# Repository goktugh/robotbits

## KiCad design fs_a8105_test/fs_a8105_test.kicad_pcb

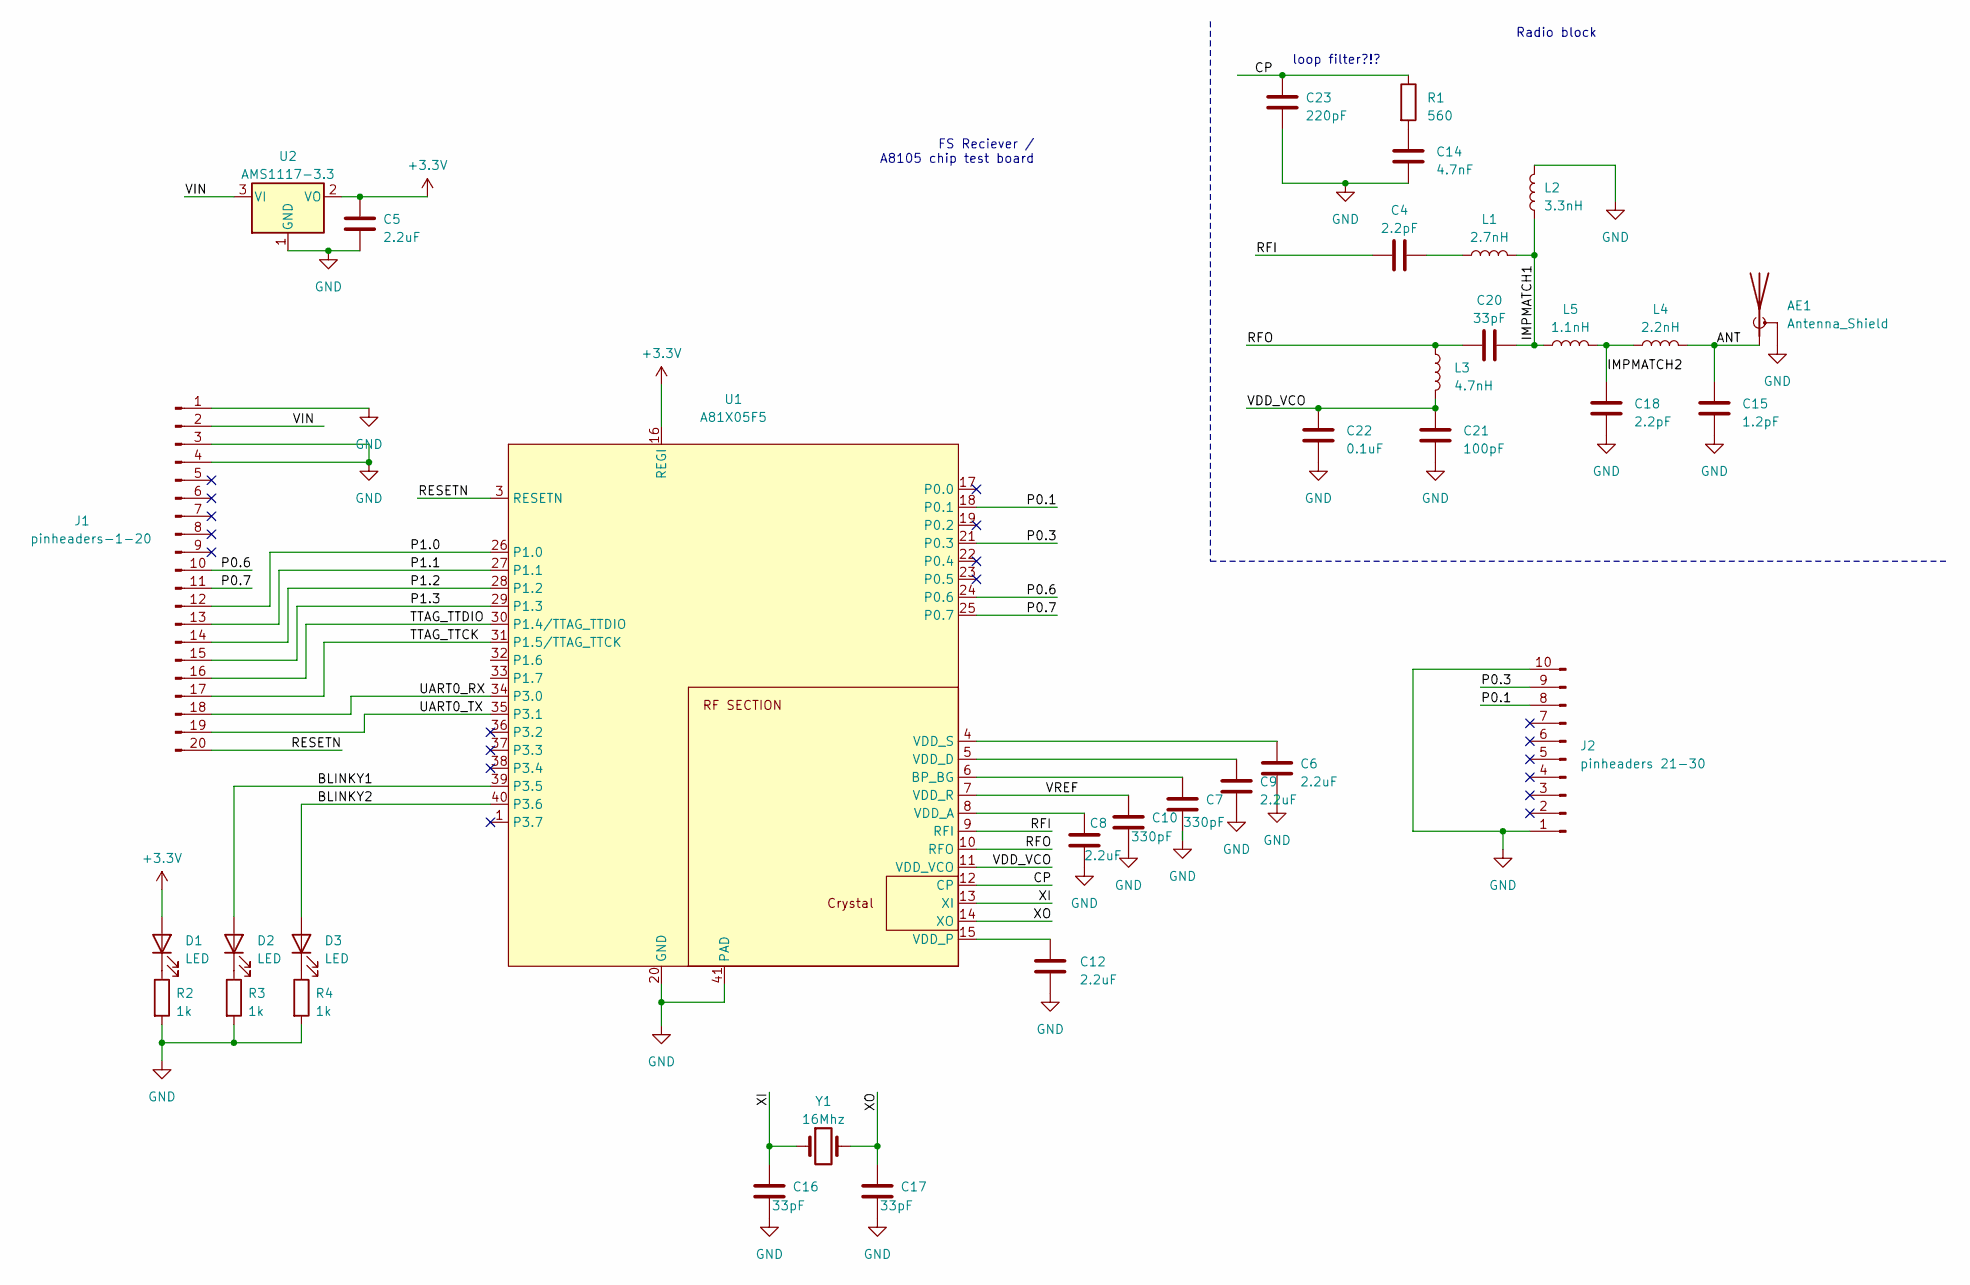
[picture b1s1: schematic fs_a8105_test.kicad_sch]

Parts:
AE1: Antenna_Shield; Texas_SWRA117D_2.4GHz_Right
C4, C18: 2.2pF; C_0603_1608Metric
C5, C6, C8, C9, C12: 2.2uF; C_0603_1608Metric
C7, C10: 330pF; C_0603_1608Metric
C14: 4.7nF; C_0603_1608Metric
C15: 1.2pF; C_0603_1608Metric
C16, C17, C20: 33pF; C_0603_1608Metric
C21: 100pF; C_0603_1608Metric
C22: 0.1uF; C_0603_1608Metric
C23: 220pF; C_0603_1608Metric
D1, D2, D3: LED; LED_0603_1608Metric_Pad1.05x0.95mm_HandSolder
J1: pinheaders-1-20; PinHeader_1x20_P2.54mm_Vertical
J2: pinheaders 21-30; PinHeader_1x10_P2.54mm_Vertical
L1: 2.7nH; L_0603_1608Metric
L2: 3.3nH; L_0603_1608Metric
L3: 4.7nH; L_0603_1608Metric
L4: 2.2nH; L_0603_1608Metric
L5: 1.1nH; L_0603_1608Metric
R1: 560; R_0603_1608Metric
R2, R3, R4: 1k; R_0603_1608Metric
U1: A81X05F5; QFN-40-A8105-longpads
U2: AMS1117-3.3; SOT-223-3_TabPin2
Y1: 16Mhz; Crystal_SMD_5032-2Pin_5.0x3.2mm

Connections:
+3V3: C5.1, D1.2 (A), U1.16 (REGI), U2.2 (VO)
/ANT: AE1.1 (A), C15.1, L4.2
/BLINKY1: D2.2 (A), U1.39 (P3.5)
/BLINKY2: D3.2 (A), U1.40 (P3.6)
/CP: C23.1, R1.1, U1.12 (CP)
/IMPMATCH1: C20.2, L1.2, L2.1, L5.1
/IMPMATCH2: C18.1, L4.1, L5.2
/P0.1: J2.8, U1.18 (P0.1)
/P0.3: J2.9, U1.21 (P0.3)
/P0.6: J1.10, U1.24 (P0.6)
/P0.7: J1.11, U1.25 (P0.7)
/P1.0: J1.12, U1.26 (P1.0)
/P1.1: J1.13, U1.27 (P1.1)
/P1.2: J1.14, U1.28 (P1.2)
/P1.3: J1.15, U1.29 (P1.3)
/RESETN: J1.20, U1.3 (RESETN)
/RFI: C4.1, U1.9 (RFI)
/RFO: C20.1, L3.1, U1.10 (RFO)
/TTAG_TTCK: J1.17, U1.31 (P1.5/TTAG_TTCK)
/TTAG_TTDIO: J1.16, U1.30 (P1.4/TTAG_TTDIO)
/UART0_RX: J1.18, U1.34 (P3.0)
/UART0_TX: J1.19, U1.35 (P3.1)
/VDD_VCO: C21.1, C22.1, L3.2, U1.11 (VDD_VCO)
/VIN: J1.2, U2.3 (VI)
/VREF: C10.1, U1.7 (VDD_R)
/XI: C16.1, U1.13 (XI), Y1.1
/XO: C17.1, U1.14 (XO), Y1.2
GND: AE1.2 (Shield), C5.2, C6.2, C7.2, C8.2, C9.2, C10.2, C12.2, C14.2, C15.2, C16.2, C17.2, C18.2, C21.2, C22.2, C23.2, J1.1, J1.3, J1.4, J2.1, J2.10, L2.2, R2.2, R3.2, R4.2, U1.20 (GND), U1.41 (PAD), U2.1 (GND)
unnamed: C4.2, L1.1
unnamed: C6.1, U1.4 (VDD_S)
unnamed: C7.1, U1.6 (BP_BG)
unnamed: C8.1, U1.8 (VDD_A)
unnamed: C9.1, U1.5 (VDD_D)
unnamed: C12.1, U1.15 (VDD_P)
unnamed: C14.1, R1.2
unnamed: D1.1 (K), R2.1
unnamed: D2.1 (K), R3.1
unnamed: D3.1 (K), R4.1

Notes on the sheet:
FS Reciever / A8105 chip test board
loop filter?!?
Radio block

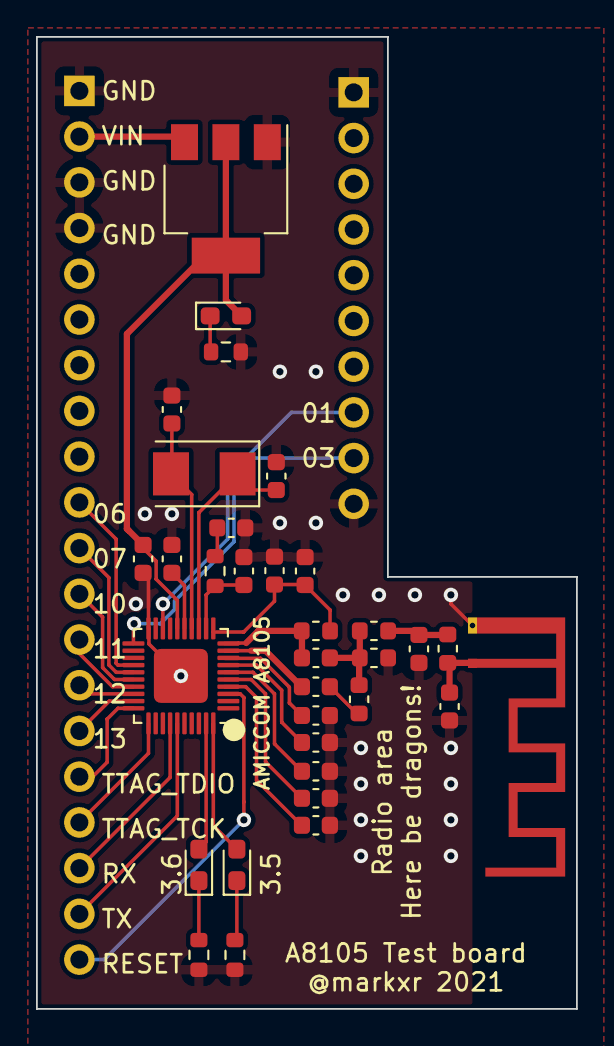
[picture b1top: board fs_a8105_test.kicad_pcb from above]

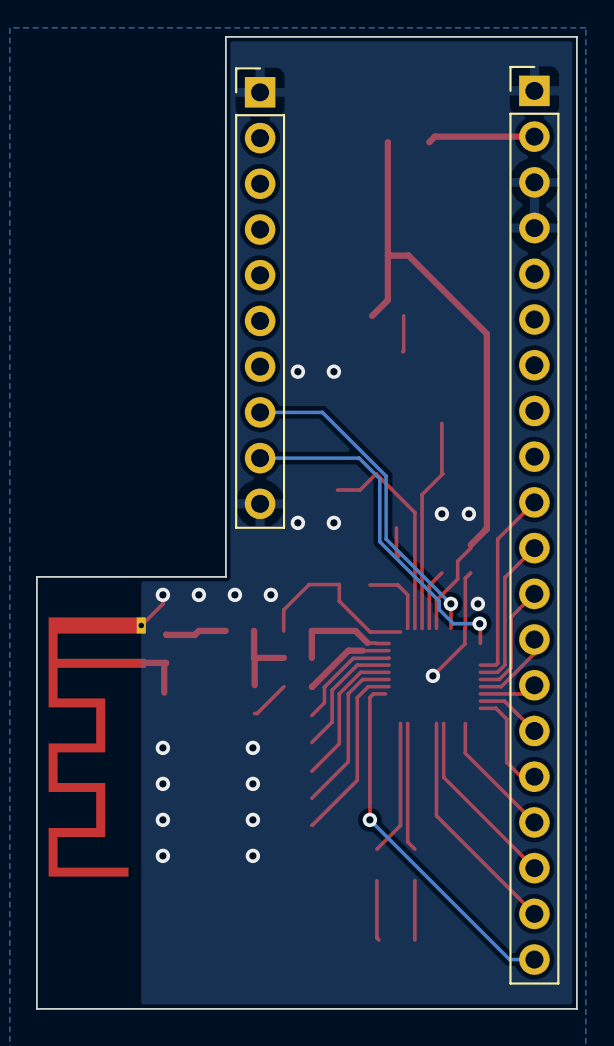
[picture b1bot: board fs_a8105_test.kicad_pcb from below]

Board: 2 copper layers, 30.0 x 54.0 mm, 35 parts (2 on the bottom side), 38 nets.

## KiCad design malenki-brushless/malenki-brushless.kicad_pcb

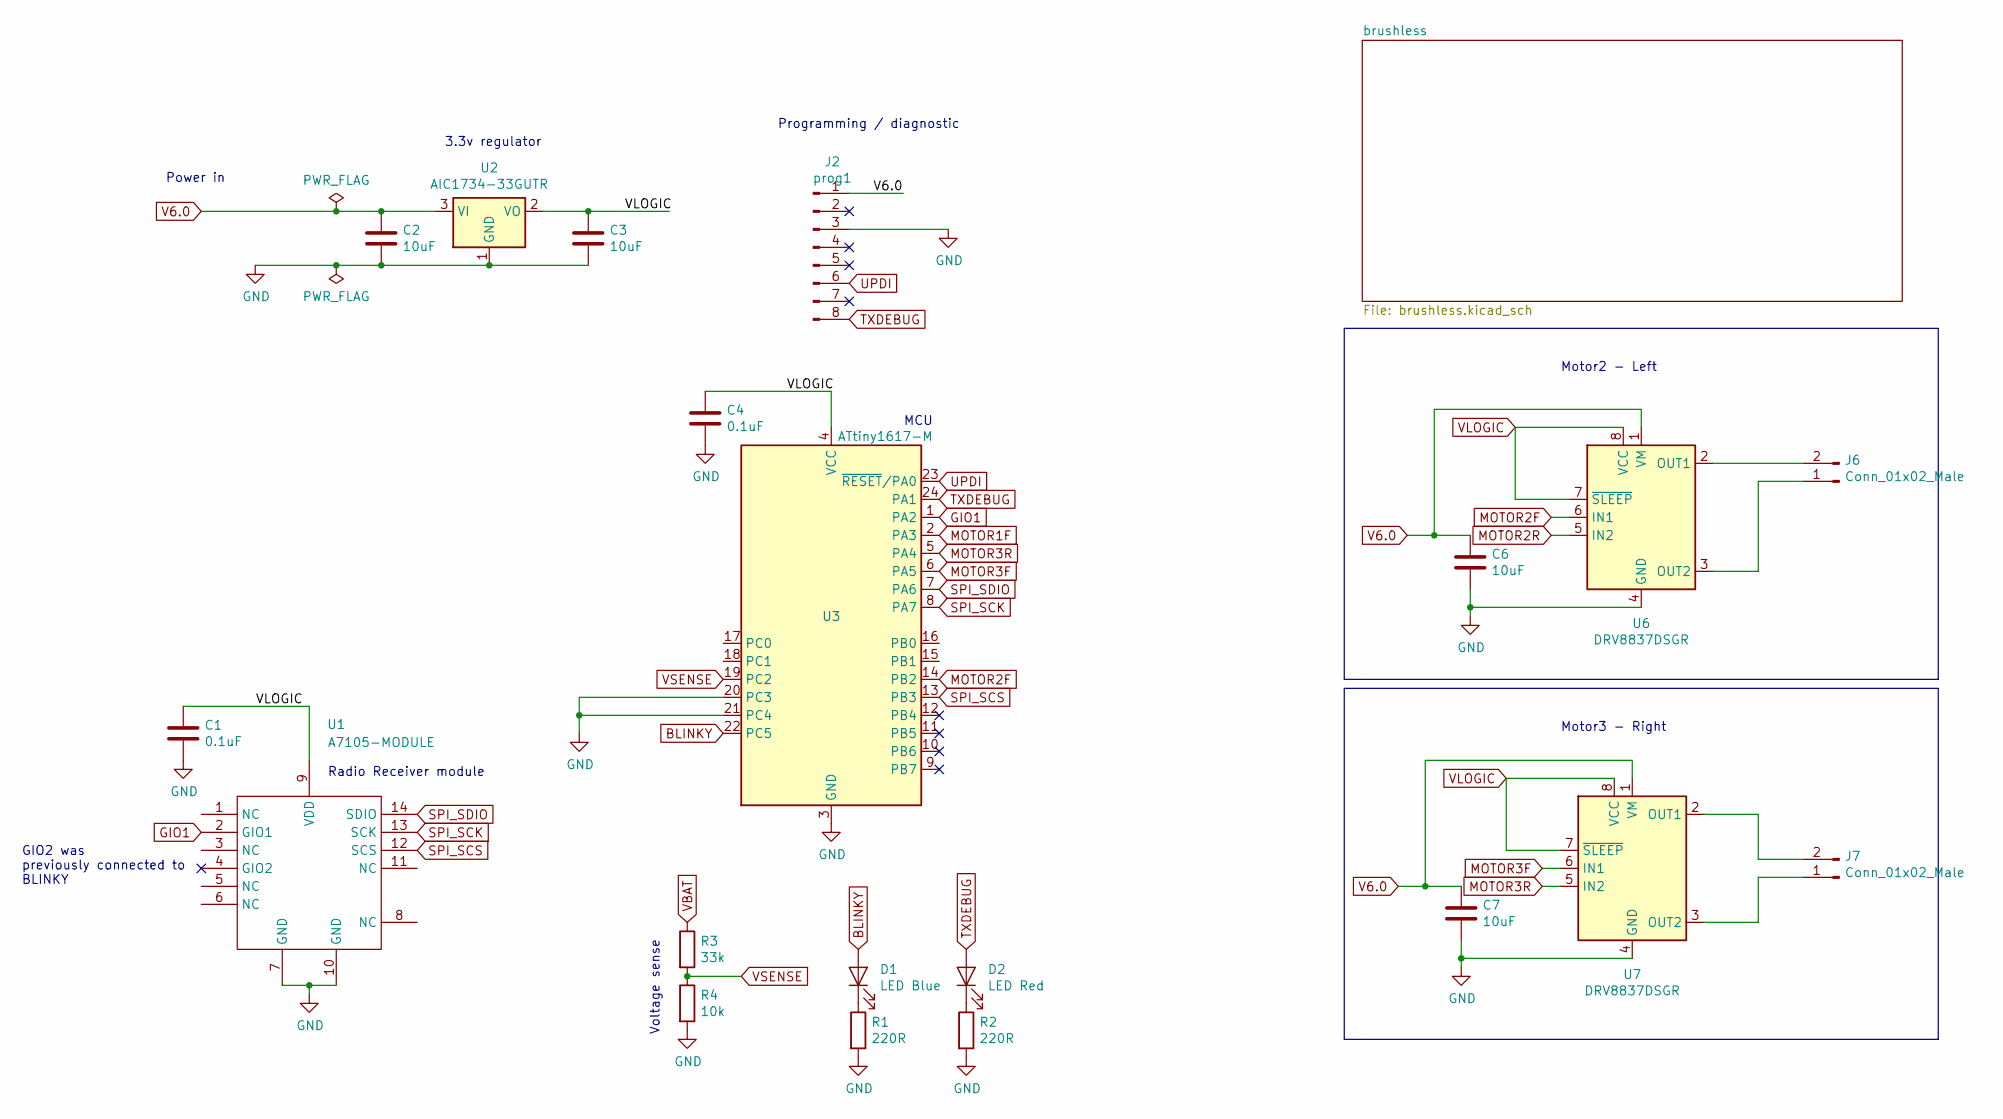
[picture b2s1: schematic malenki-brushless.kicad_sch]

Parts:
C1, C4: 0.1uF; C_0603_1608Metric; Partnum C14663; LCSC C14663
C2, C3, C6, C7: 10uF; C_0603_1608Metric; LCSC C19702
D1: LED Blue; LED_0805_2012Metric_Castellated; LCSC C2293
D2: LED Red; LED_0805_2012Metric_Castellated; LCSC C84256
J2: prog1; SOIC_clipProgSmall
J6, J7: Conn_01x02_Male; PinHeader_1x02_P2.54mm_BIG1
R1, R2: 220R; R_0603_1608Metric; Partnum C22962; LCSC C22962
R3: 33k; R_0603_1608Metric; Partnum C4216; LCSC C4216
R4: 10k; R_0603_1608Metric; Partnum C25804; LCSC C25804
U1: A7105-MODULE; A7105-module
U2: AIC1734-33GUTR; SOT-23; Partnum C211659; LCSC C211659
U3: ATtiny1617-M; qfn24-hand1; Partnum C194193; LCSC C194193
U6, U7: DRV8837DSGR; WSON-8-1EP_2x2mm_P0.5mm_HAND1; LCSC C39159

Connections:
BLINKY: D1.2 (A), U3.22 (PC5)
GIO1: U1.2 (GIO1), U3.1 (PA2)
GND: C1.2, C2.2, C3.2, C4.2, C6.2, C7.2, J2.3, R1.2, R2.2, R4.2, U1.7 (GND), U1.10 (GND), U2.1 (GND), U3.3 (GND), U3.20 (PC3), U3.21 (PC4), U3.25 (GND), U6.4 (GND), U6.9 (GND), U7.4 (GND), U7.9 (GND); also elsewhere on the board
MOTOR1F: U3.2 (PA3)
MOTOR2F: U3.14 (PB2), U6.6 (IN1)
MOTOR2R: U6.5 (IN2)
MOTOR3F: U3.6 (PA5), U7.6 (IN1)
MOTOR3R: U3.5 (PA4), U7.5 (IN2)
unnamed: D1.1 (K), R1.1
unnamed: D2.1 (K), R2.1
unnamed: J6.1, U6.3 (OUT2)
unnamed: J6.2, U6.2 (OUT1)
unnamed: J7.1, U7.3 (OUT2)
unnamed: J7.2, U7.2 (OUT1)
SPI_SCK: U1.13 (SCK), U3.8 (PA7)
SPI_SCS: U1.12 (SCS), U3.13 (PB3)
SPI_SDIO: U1.14 (SDIO), U3.7 (PA6)
TXDEBUG: D2.2 (A), J2.8, U3.24 (PA1)
UPDI: J2.6, U3.23 (~RESET~/PA0)
V6.0: C2.1, C6.1, C7.1, J2.1, U2.3 (VI), U6.1 (VM), U7.1 (VM); also elsewhere on the board
VBAT: R3.1; also elsewhere on the board
VLOGIC: C1.1, C3.1, C4.1, U1.9 (VDD), U2.2 (VO), U3.4 (VCC), U6.7 (~SLEEP), U6.8 (VCC), U7.7 (~SLEEP), U7.8 (VCC)
VSENSE: R3.2, R4.1, U3.19 (PC2)

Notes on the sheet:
GIO2 was previously connected to BLINKY
Power in
Radio Receiver module
3.3v regulator
Voltage sense
Programming / diagnostic
MCU
Motor2 - Left
Motor3 - Right

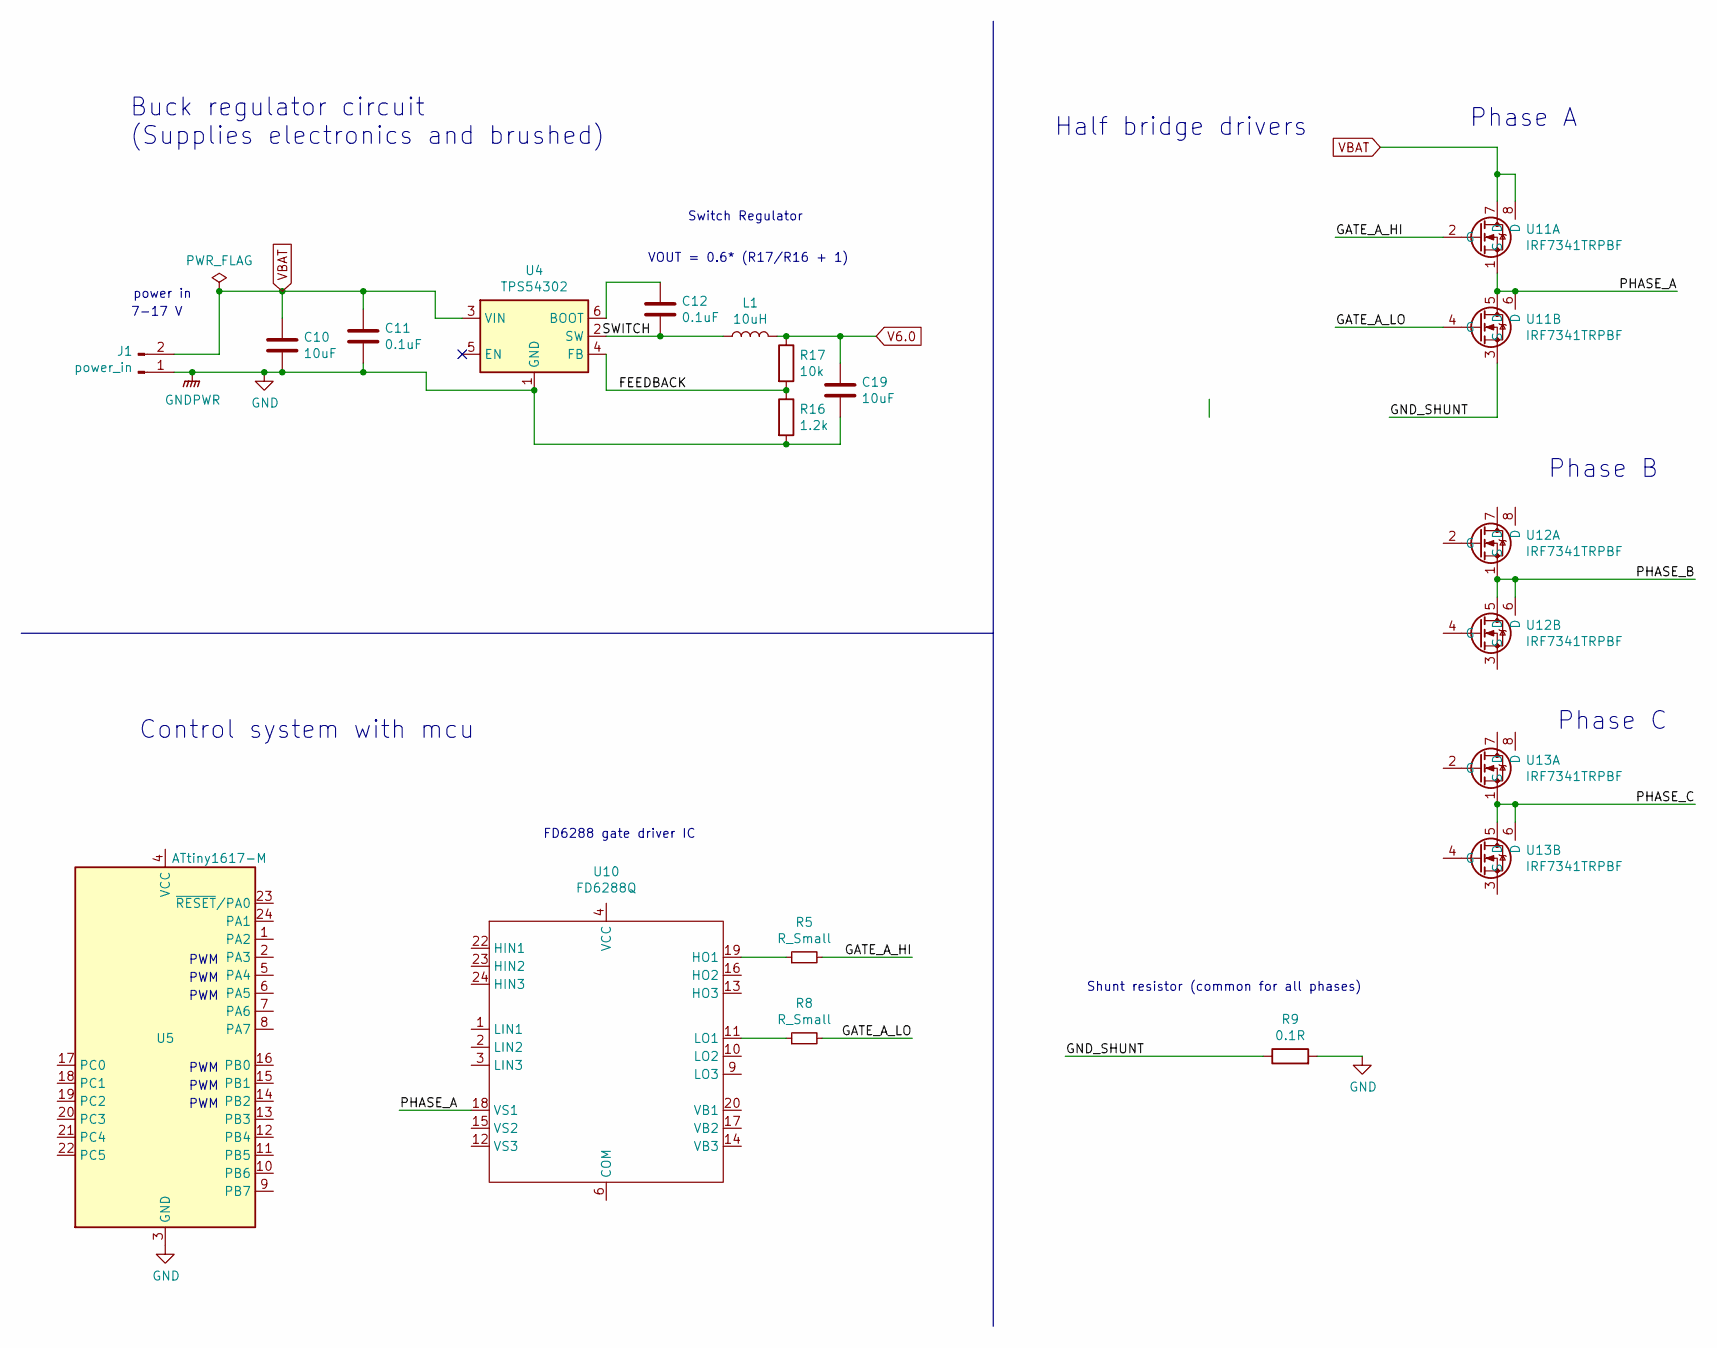
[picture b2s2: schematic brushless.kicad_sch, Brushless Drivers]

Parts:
C10, C19: 10uF; C_1210_3225Metric
C11, C12: 0.1uF; C_1206_3216Metric
J1: power_in; SolderWirePad_1x02_P7.62mm_Drill2mm
L1: 10uH; L_6.3x6.3_H3
R5, R8: R_Small; R_0603_1608Metric
R9: 0.1R; R_1218_3246Metric
R16: 1.2k; R_0805_2012Metric
R17: 10k; R_0805_2012Metric
U4: TPS54302; SOT-23-6
U5: ATtiny1617-M; qfn24-hand1; Partnum C194193; LCSC C194193
U10: FD6288Q; QFN-24-1EP_4x4mm_P0.5mm_EP2.65x2.65mm
U11, U12, U13: IRF7341TRPBF; SOIC-8_3.9x4.9mm_P1.27mm

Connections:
/brushless/FEEDBACK: R16.1, R17.2, U4.4 (FB)
/brushless/GATE_A_HI: R5.2, U11.2 (G)
/brushless/GATE_A_LO: R8.2, U11.4 (G)
/brushless/GND_SHUNT: R9.1, U11.3 (S)
/brushless/PHASE_A: U10.18 (VS1), U11.1 (S), U11.5 (D), U11.6 (D)
/brushless/PHASE_B: U12.1 (S), U12.5 (D), U12.6 (D)
/brushless/PHASE_C: U13.1 (S), U13.5 (D), U13.6 (D)
/brushless/SWITCH: C12.2, L1.1, U4.2 (SW)
GND: C10.2, C11.2, C19.2, J1.1, R9.2, R16.2, U4.1 (GND), U5.3 (GND), U5.25 (GND); also elsewhere on the board
unnamed: C12.1, U4.6 (BOOT)
unnamed: R5.1, U10.19 (HO1)
unnamed: R8.1, U10.11 (LO1)
V6.0: C19.1, L1.2, R17.1; also elsewhere on the board
VBAT: C10.1, C11.1, J1.2, U4.3 (VIN), U11.7 (D), U11.8 (D); also elsewhere on the board

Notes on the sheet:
Buck regulator circuit (Supplies electronics and brushed)
Control system with mcu
7-17 V
power in
PWM
Switch Regulator
FD6288 gate driver IC
VOUT = 0.6* (R17/R16 + 1)
Half bridge drivers
Shunt resistor (common for all phases)
Phase A
Phase B
Phase C

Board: 2 copper layers, 36 parts (2 on the bottom side), 32 nets, no tracks yet.

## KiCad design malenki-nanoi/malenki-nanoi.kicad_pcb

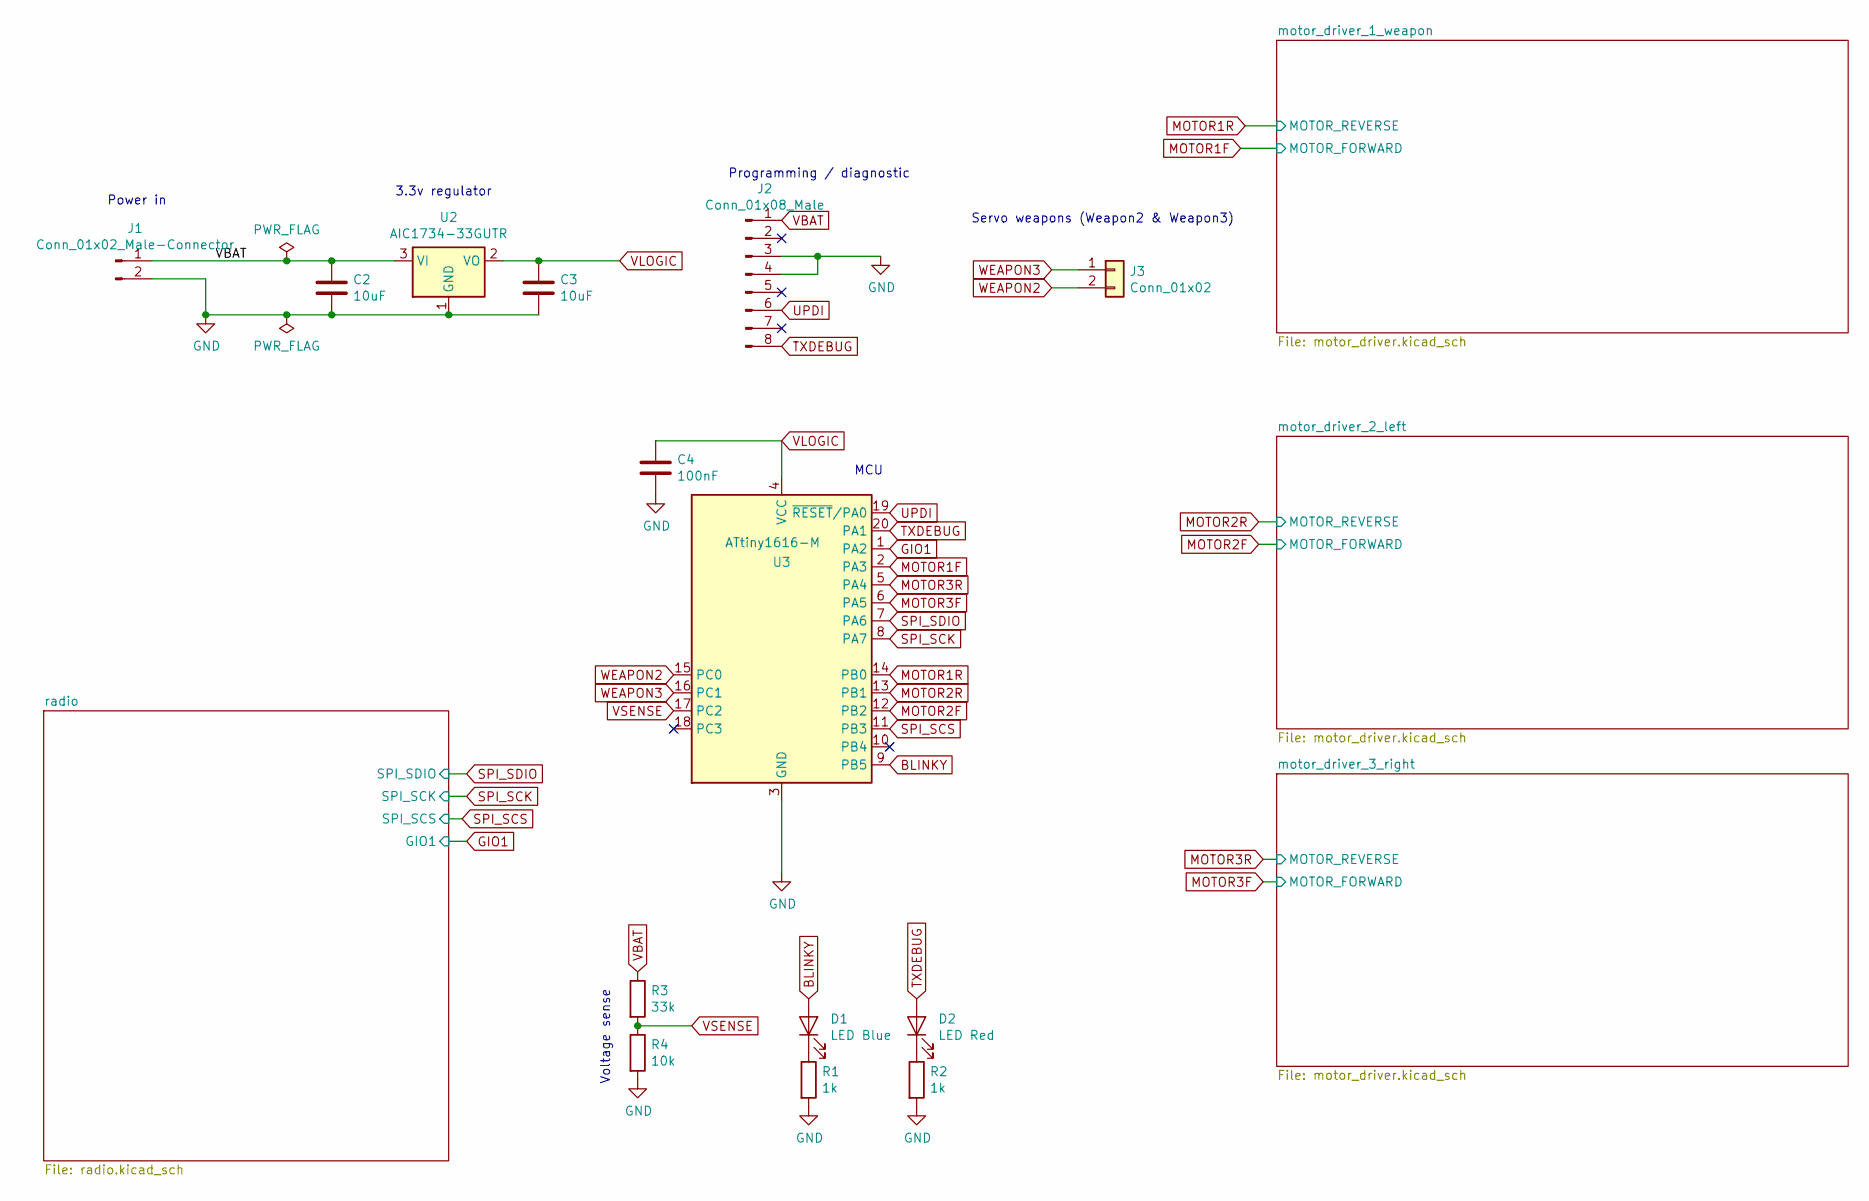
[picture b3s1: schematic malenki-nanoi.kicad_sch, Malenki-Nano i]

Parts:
C2, C3: 10uF; C_0603_1608Metric; MPN CL10A106KP8NNNC; LCSC C19702
C4: 100nF; C_0402_1005Metric_Pad0.74x0.62mm_HandSolder; Partnum C14663; LCSC C1525
D1: LED Blue; LED_0603_1608Metric; MPN 19-217/BHC-ZL1M2RY/3T; LCSC C72041
D2: LED Red; LED_0603_1608Metric; MPN KT-0603R; LCSC C2286
J1: Conn_01x02_Male-Connector; PinHeader_1x02_P2.54mm_BIG1
J2: Conn_01x08_Male; SOIC_clipProgSmall
J3: Conn_01x02; wirepad_2
R1, R2: 1k; R_0603_1608Metric; MPN 0603WAF1001T5E; LCSC C21190
R3: 33k; R_0603_1608Metric; Partnum C4216; LCSC C4216
R4: 10k; R_0603_1608Metric; Partnum C25804; LCSC C25804
U2: AIC1734-33GUTR; SOT-23; Partnum C211659; LCSC C211659
U3: ATtiny1616-M; VQFN-20-1EP_3x3mm_P0.4mm_EP1.7x1.7mm; MPN ATtiny1616-MNR

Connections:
BLINKY: D1.2 (A), U3.9 (PB5)
GIO1: U3.1 (PA2); also elsewhere on the board
GND: C2.2, C3.2, C4.2, J1.2, J2.3, J2.4, R1.2, R2.2, R4.2, U2.1 (GND), U3.3 (GND), U3.21 (GND); also elsewhere on the board
MOTOR1F: U3.2 (PA3); also elsewhere on the board
MOTOR1R: U3.14 (PB0); also elsewhere on the board
MOTOR2F: U3.12 (PB2); also elsewhere on the board
MOTOR2R: U3.13 (PB1); also elsewhere on the board
MOTOR3F: U3.6 (PA5); also elsewhere on the board
MOTOR3R: U3.5 (PA4); also elsewhere on the board
unnamed: D1.1 (K), R1.1
unnamed: D2.1 (K), R2.1
SPI_SCK: U3.8 (PA7); also elsewhere on the board
SPI_SCS: U3.11 (PB3); also elsewhere on the board
SPI_SDIO: U3.7 (PA6); also elsewhere on the board
TXDEBUG: D2.2 (A), J2.8, U3.20 (PA1)
UPDI: J2.6, U3.19 (~RESET~/PA0)
VBAT: C2.1, J1.1, J2.1, R3.1, U2.3 (VI); also elsewhere on the board
VLOGIC: C3.1, C4.1, U2.2 (VO), U3.4 (VCC); also elsewhere on the board
VSENSE: R3.2, R4.1, U3.17 (PC2)
WEAPON2: J3.2, U3.15 (PC0)
WEAPON3: J3.1, U3.16 (PC1)
no_connect_41: J2.2
no_connect_42: J2.5
no_connect_43: J2.7
no_connect_46: U3.10 (PB4)
no_connect_47: U3.18 (PC3)

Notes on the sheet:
Power in
3.3v regulator
Voltage sense
Programming / diagnostic
MCU
Servo weapons (Weapon2 & Weapon3)

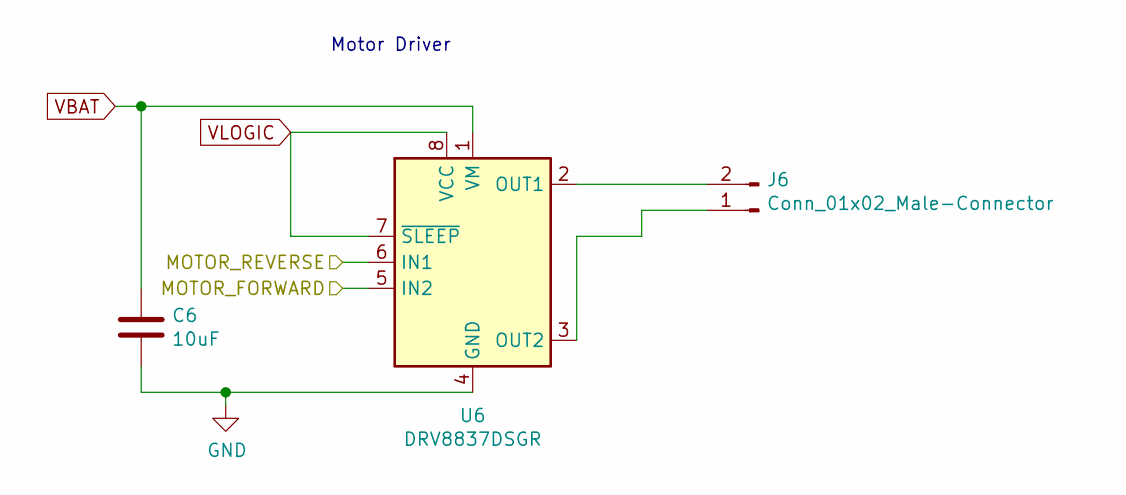
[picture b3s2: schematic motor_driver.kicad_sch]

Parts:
C6: 10uF; C_0603_1608Metric; MPN CL10A106KP8NNNC; LCSC C19702
J6: Conn_01x02_Male-Connector; PinHeader_1x02_P2.54mm_BIG1
U6: DRV8837DSGR; WSON-8-1EP_2x2mm_P0.5mm_HAND1; MPN DRV8837DSGR; LCSC C39159

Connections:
GND: C6.2, U6.4 (GND), U6.9 (GND); also elsewhere on the board
MOTOR3F: U6.5 (IN2); also elsewhere on the board
MOTOR3R: U6.6 (IN1); also elsewhere on the board
unnamed: J6.1, U6.3 (OUT2)
unnamed: J6.2, U6.2 (OUT1)
VBAT: C6.1, U6.1 (VM); also elsewhere on the board
VLOGIC: U6.7 (~SLEEP), U6.8 (VCC); also elsewhere on the board

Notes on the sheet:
Motor Driver

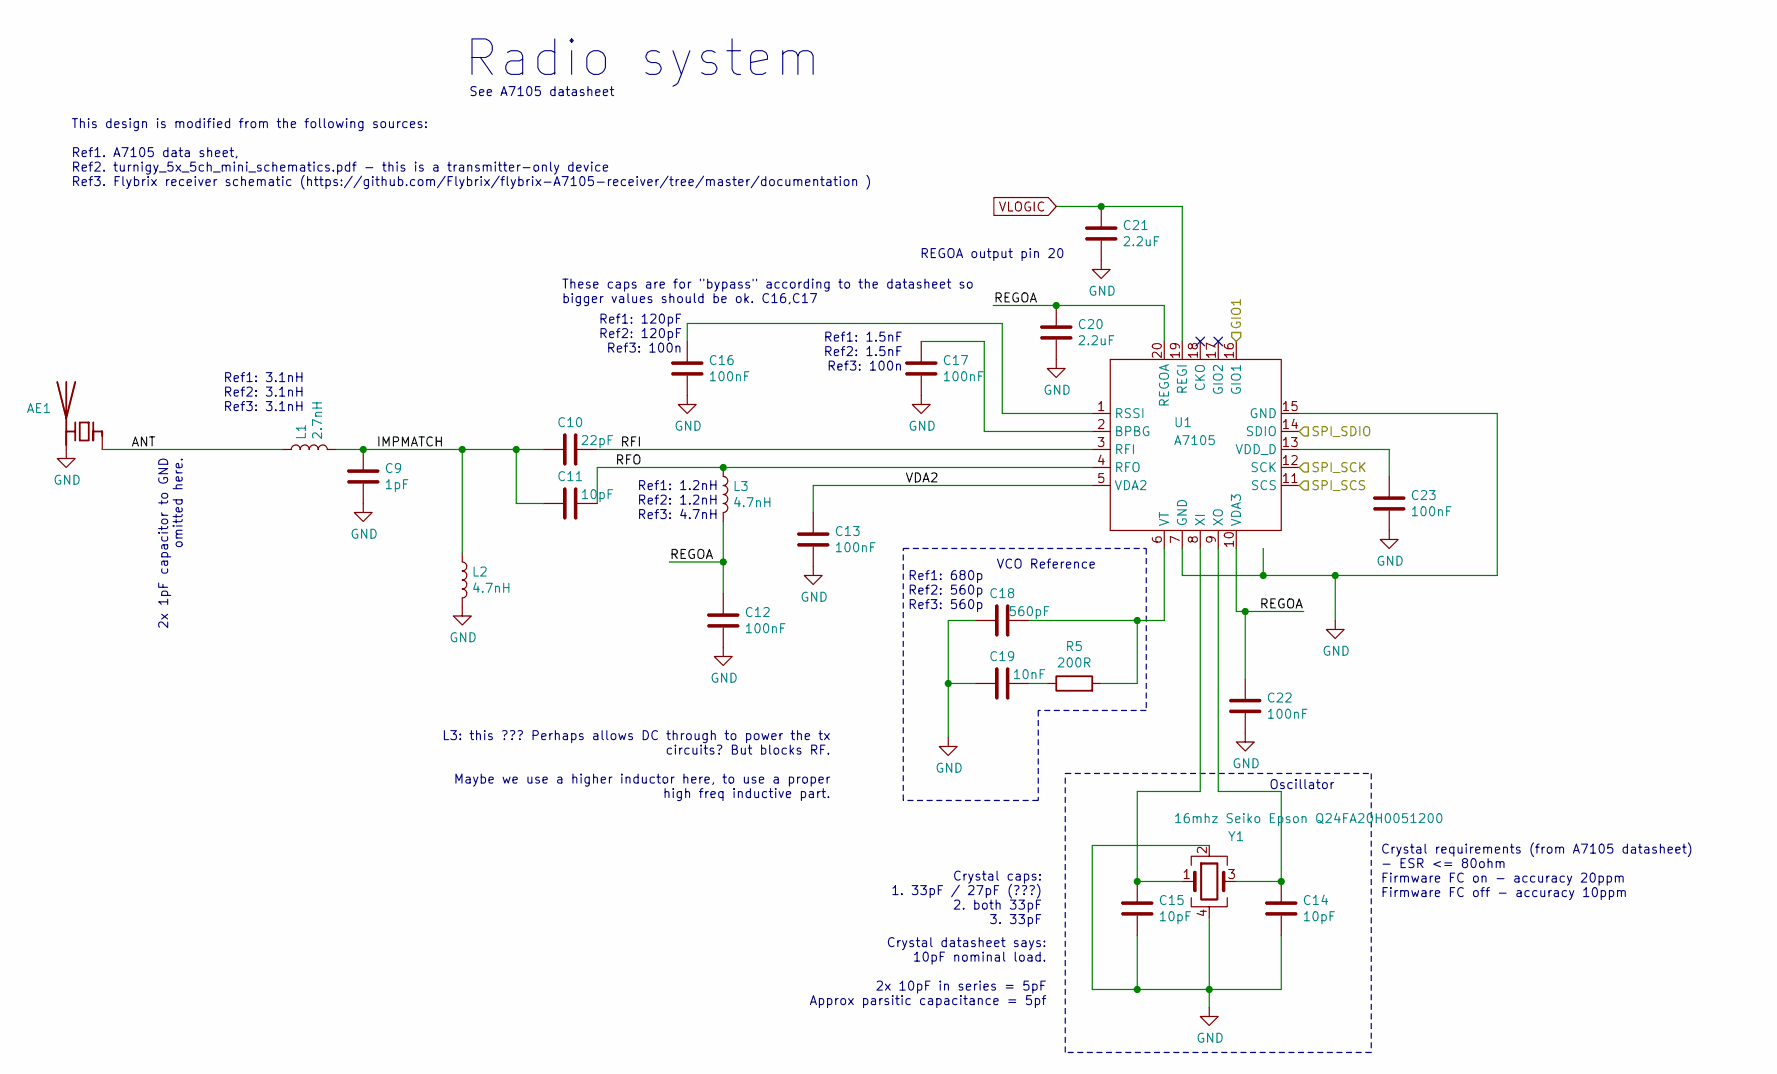
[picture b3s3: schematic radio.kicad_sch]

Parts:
AE1: Texas_SWRA117D_2.4GHz_Left
C9: 1pF; C_0402_1005Metric_Pad0.74x0.62mm_HandSolder; MPN 0402CG1R0C500NT; LCSC C1550
C10: 22pF; C_0402_1005Metric_Pad0.74x0.62mm_HandSolder; MPN 0402CG220J500NT; LCSC C1555
C11, C14, C15: 10pF; C_0402_1005Metric_Pad0.74x0.62mm_HandSolder; MPN CL05C100JB5NNNC; LCSC C32949
C12, C13, C16, C17, C22, C23: 100nF; C_0402_1005Metric_Pad0.74x0.62mm_HandSolder; MPN CL05B104KO5NNNC; LCSC C1525
C18: 560pF; C_0402_1005Metric_Pad0.74x0.62mm_HandSolder; MPN CL05C561JB5NNNC; LCSC C318606
C19: 10nF; C_0402_1005Metric_Pad0.74x0.62mm_HandSolder; MPN CL05B103KB5NNNC; LCSC C15195
C20, C21: 2.2uF; C_0603_1608Metric; MPN CL05A225MQ5NSNC; LCSC C12530
L1: 2.7nH; L_0402_1005Metric_Pad0.77x0.64mm_HandSolder; MPN SDCL1608C2N7STDF; LCSC C13817
L2, L3: 4.7nH; L_0402_1005Metric_Pad0.77x0.64mm_HandSolder; MPN VHF160808H4N7ST; LCSC C1030
R5: 200R; R_0402_1005Metric_Pad0.72x0.64mm_HandSolder; MPN 0402WGF2000TCE; LCSC C25087
U1: A7105; a7105-QFN-20; MPN A71X05AQFI/Q; LCSC C126376
Y1: 16mhz Seiko Epson Q24FA20H0051200; Crystal_SMD_2520-4Pin_2.5x2.0mm; MPN Q24FA20H0051200; LCSC C255947

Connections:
/radio/ANT: AE1.1 (FEED), L1.1
/radio/IMPMATCH: C9.1, C10.1, C11.1, L1.2, L2.1
/radio/REGOA: C12.1, C20.1, C22.1, L3.2, U1.10 (VDA3), U1.20 (REGOA)
/radio/RFI: C10.2, U1.3 (RFI)
/radio/RFO: C11.2, L3.1, U1.4 (RFO)
/radio/VDA2: C13.1, U1.5 (VDA2)
GIO1: U1.16 (GIO1); also elsewhere on the board
GND: AE1.2 (PCB_Trace), C9.2, C12.2, C13.2, C14.2, C15.2, C16.2, C17.2, C18.1, C19.2, C20.2, C21.2, C22.2, C23.2, L2.2, U1.7 (GND), U1.15 (GND), U1.21 (GND), Y1.2, Y1.4; also elsewhere on the board
unnamed: C14.1, U1.9 (XO), Y1.3
unnamed: C15.1, U1.8 (XI), Y1.1
unnamed: C16.1, U1.1 (RSSI)
unnamed: C17.1, U1.2 (BPBG)
unnamed: C18.2, R5.2, U1.6 (VT)
unnamed: C19.1, R5.1
unnamed: C23.1, U1.13 (VDD_D)
SPI_SCK: U1.12 (SCK); also elsewhere on the board
SPI_SCS: U1.11 (SCS); also elsewhere on the board
SPI_SDIO: U1.14 (SDIO); also elsewhere on the board
VLOGIC: C21.1, U1.19 (REGI); also elsewhere on the board
no_connect_44: U1.17 (GIO2)
no_connect_45: U1.18 (CKO)

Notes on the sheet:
This design is modified from the following sources: Ref1. A7105 data sheet, Ref2. turnigy_5x_5ch_mini_schematics.pdf - this is a transmitter-only device Ref3. Flybrix receiver schematic (https://github.com/Flybrix/flybrix-A7105-receiver/tree/master/documentation )
2x 1pF capacitor to GND omitted here.
Ref1: 3.1nH Ref2: 3.1nH Ref3: 3.1nH
These caps are for "bypass" according to the datasheet so bigger values should be ok. C16,C17
See A7105 datasheet
Ref1: 120pF Ref2: 120pF Ref3: 100n
Ref1: 1.2nH Ref2: 1.2nH Ref3: 4.7nH
Radio system
L3: this ??? Perhaps allows DC through to power the tx circuits? But blocks RF. Maybe we use a higher inductor here, to use a proper high freq inductive part.
Ref1: 1.5nF Ref2: 1.5nF Ref3: 100n
Ref1: 680p Ref2: 560p Ref3: 560p
Crystal caps: 1. 33pF / 27pF (???) 2. both 33pF 3. 33pF
Crystal datasheet says: 10pF nominal load. 2x 10pF in series = 5pF Approx parsitic capacitance = 5pf
REGOA output pin 20
VCO Reference
Oscillator
Crystal requirements (from A7105 datasheet) - ESR <= 80ohm Firmware FC on - accuracy 20ppm Firmware FC off - accuracy 10ppm

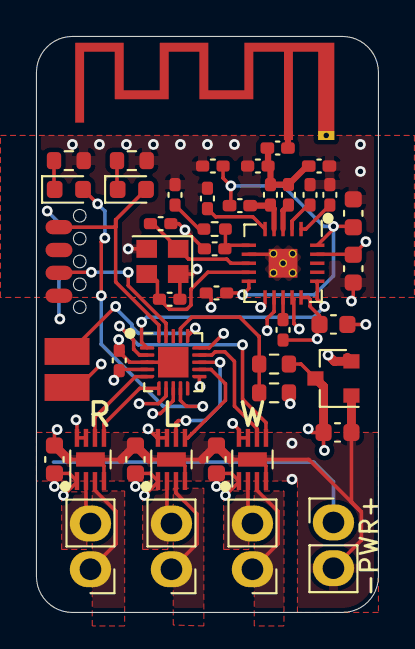
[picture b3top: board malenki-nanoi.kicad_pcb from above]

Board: 4 copper layers, 19.0 x 32.0 mm, 45 parts (1 on the bottom side), 40 nets.

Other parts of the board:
C1, C5: 10uF; C_0603_1608Metric
J4, J5: Conn_01x02_Male-Connector; PinHeader_1x02_P2.54mm_BIG1
U4, U5: DRV8837DSGR; WSON-8-1EP_2x2mm_P0.5mm_HAND1

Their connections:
GND: C1.2, C5.2, U4.4 (GND), U4.9 (GND), U5.4 (GND), U5.9 (GND); also elsewhere on the board
MOTOR1F: U4.5 (IN2); also elsewhere on the board
MOTOR1R: U4.6 (IN1); also elsewhere on the board
MOTOR2F: U5.5 (IN2); also elsewhere on the board
MOTOR2R: U5.6 (IN1); also elsewhere on the board
unnamed: J4.1, U4.3 (OUT2)
unnamed: J4.2, U4.2 (OUT1)
unnamed: J5.1, U5.3 (OUT2)
unnamed: J5.2, U5.2 (OUT1)
VBAT: C1.1, C5.1, U4.1 (VM), U5.1 (VM); also elsewhere on the board
VLOGIC: U4.7 (~SLEEP), U4.8 (VCC), U5.7 (~SLEEP), U5.8 (VCC); also elsewhere on the board
